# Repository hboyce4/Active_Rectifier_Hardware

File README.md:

Design files (Altium) for my bidirectional active rectifier. 

A Cortex-M4-driven bidirectional AC-DC power converter (active rectifier). 300W, 48VDC, 12VAC rms (through mains freq. step-down transformer). It should also be able to absorb/provide AC reactive power too. Its aim is more to be a test platform for control software than a useful/economical PSU. 

As of 2024-06-02, changes have been made to the inverter board but not incorporated into Altium because of a lack of license. They are:
 - PWModulator comparator output has been connected to GPIO PA.10 to measure duty cycle via a timer
 - U17, R56 and C87 have been removed as duty cycle is now measured digitally by a timer
 - R69 and R70 have been changed to 47 Ohm to improve rise time dramatically
 - R74, R76, R79 and R83 have all been changed to 1 Ohm to improve the power MOSFET's turn-off time

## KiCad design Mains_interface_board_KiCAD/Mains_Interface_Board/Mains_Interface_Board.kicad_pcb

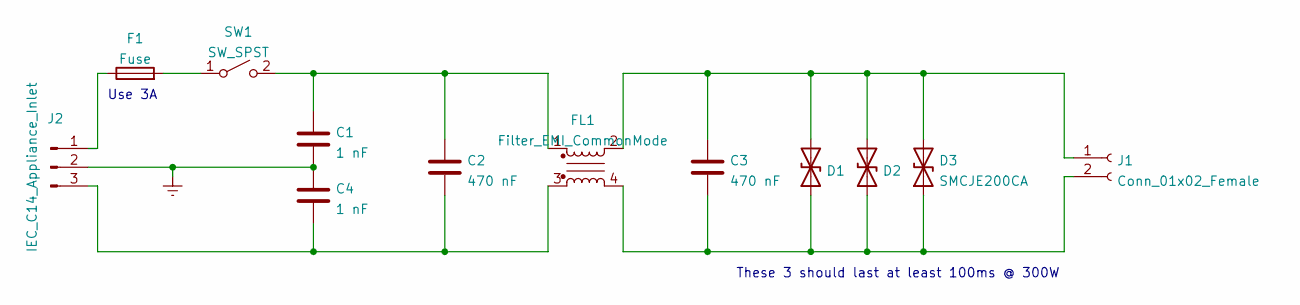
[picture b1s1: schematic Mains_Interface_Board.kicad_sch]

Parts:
C1, C4: 1 nF; C_Disc_D8.0mm_W5.0mm_P10.00mm
C2, C3: 470 nF; C_Rect_L26.5mm_W10.5mm_P22.50mm_MKS4
D1, D2, D3: SMCJE200CA; D_SMC
F1: Fuse; Fuseholder_Cylinder-6.3x30mm_Dual_Clips_Horizontal
FL1: Filter_EMI_CommonMode; Common_Mode_Choke_14x15mm
J1: Conn_01x02_Female; Dual_spades
J2: IEC_C14_Appliance_Inlet
SW1: SW_SPST; Dual_spades

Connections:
Earth: C1.2, C4.1, J2.2
unnamed: C1.1, C2.1, FL1.1, SW1.2 (B)
unnamed: C2.2, C4.2, FL1.3, J2.3
unnamed: C3.1, D1.2 (A2), D2.2 (A2), D3.2 (A2), FL1.2, J1.1
unnamed: C3.2, D1.1 (A1), D2.1 (A1), D3.1 (A1), FL1.4, J1.2
unnamed: F1.1, J2.1
unnamed: F1.2, SW1.1 (A)

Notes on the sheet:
Use 3A
These 3 should last at least 100ms @ 300W

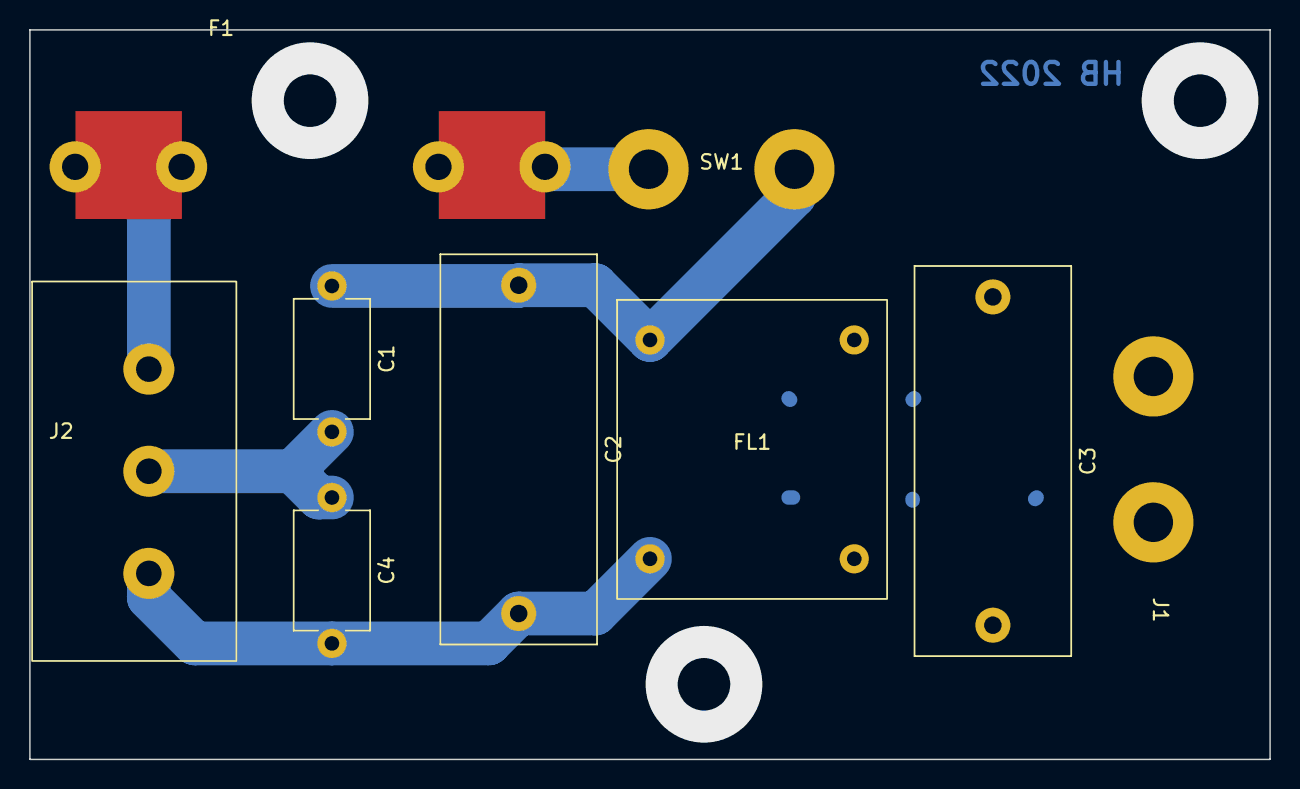
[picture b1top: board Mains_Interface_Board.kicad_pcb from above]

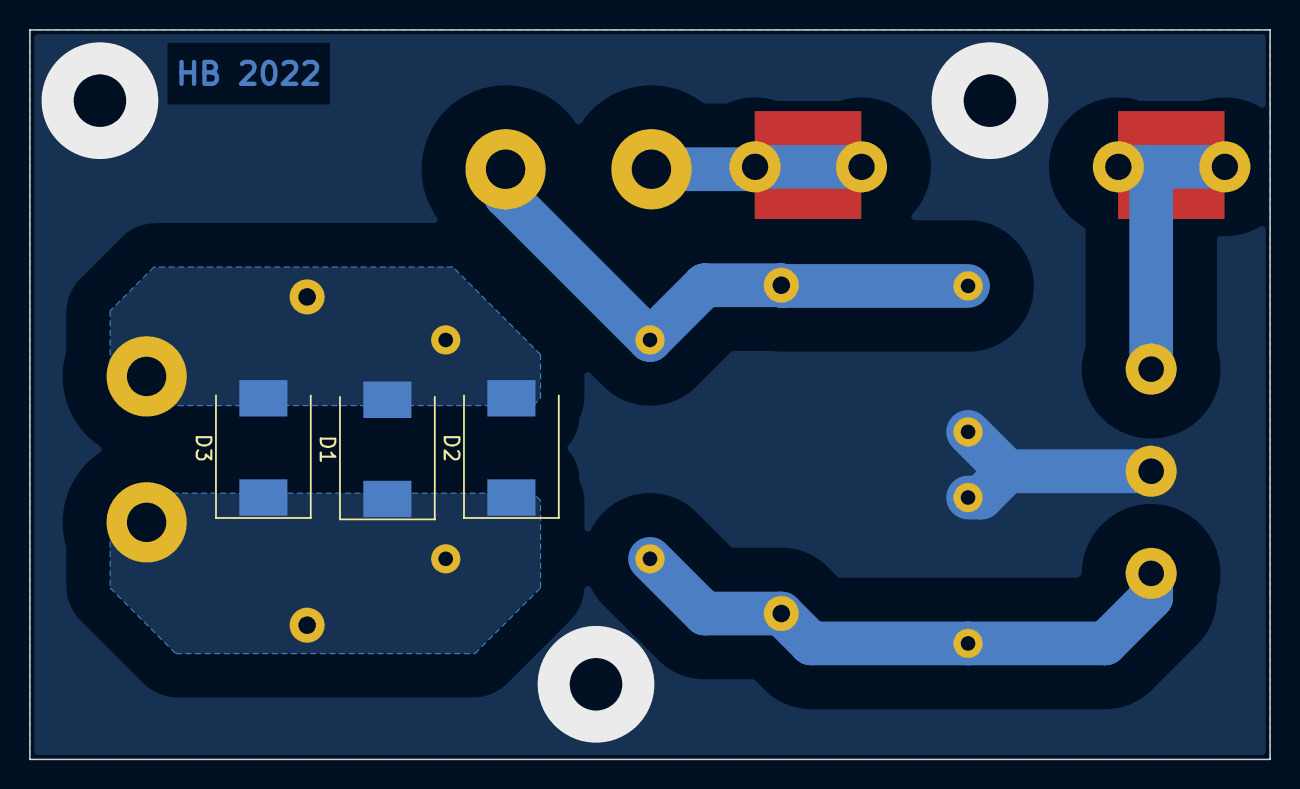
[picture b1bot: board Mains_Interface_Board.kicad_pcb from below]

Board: 2 copper layers, 85.0 x 50.0 mm, 12 parts (3 on the bottom side), 7 nets.

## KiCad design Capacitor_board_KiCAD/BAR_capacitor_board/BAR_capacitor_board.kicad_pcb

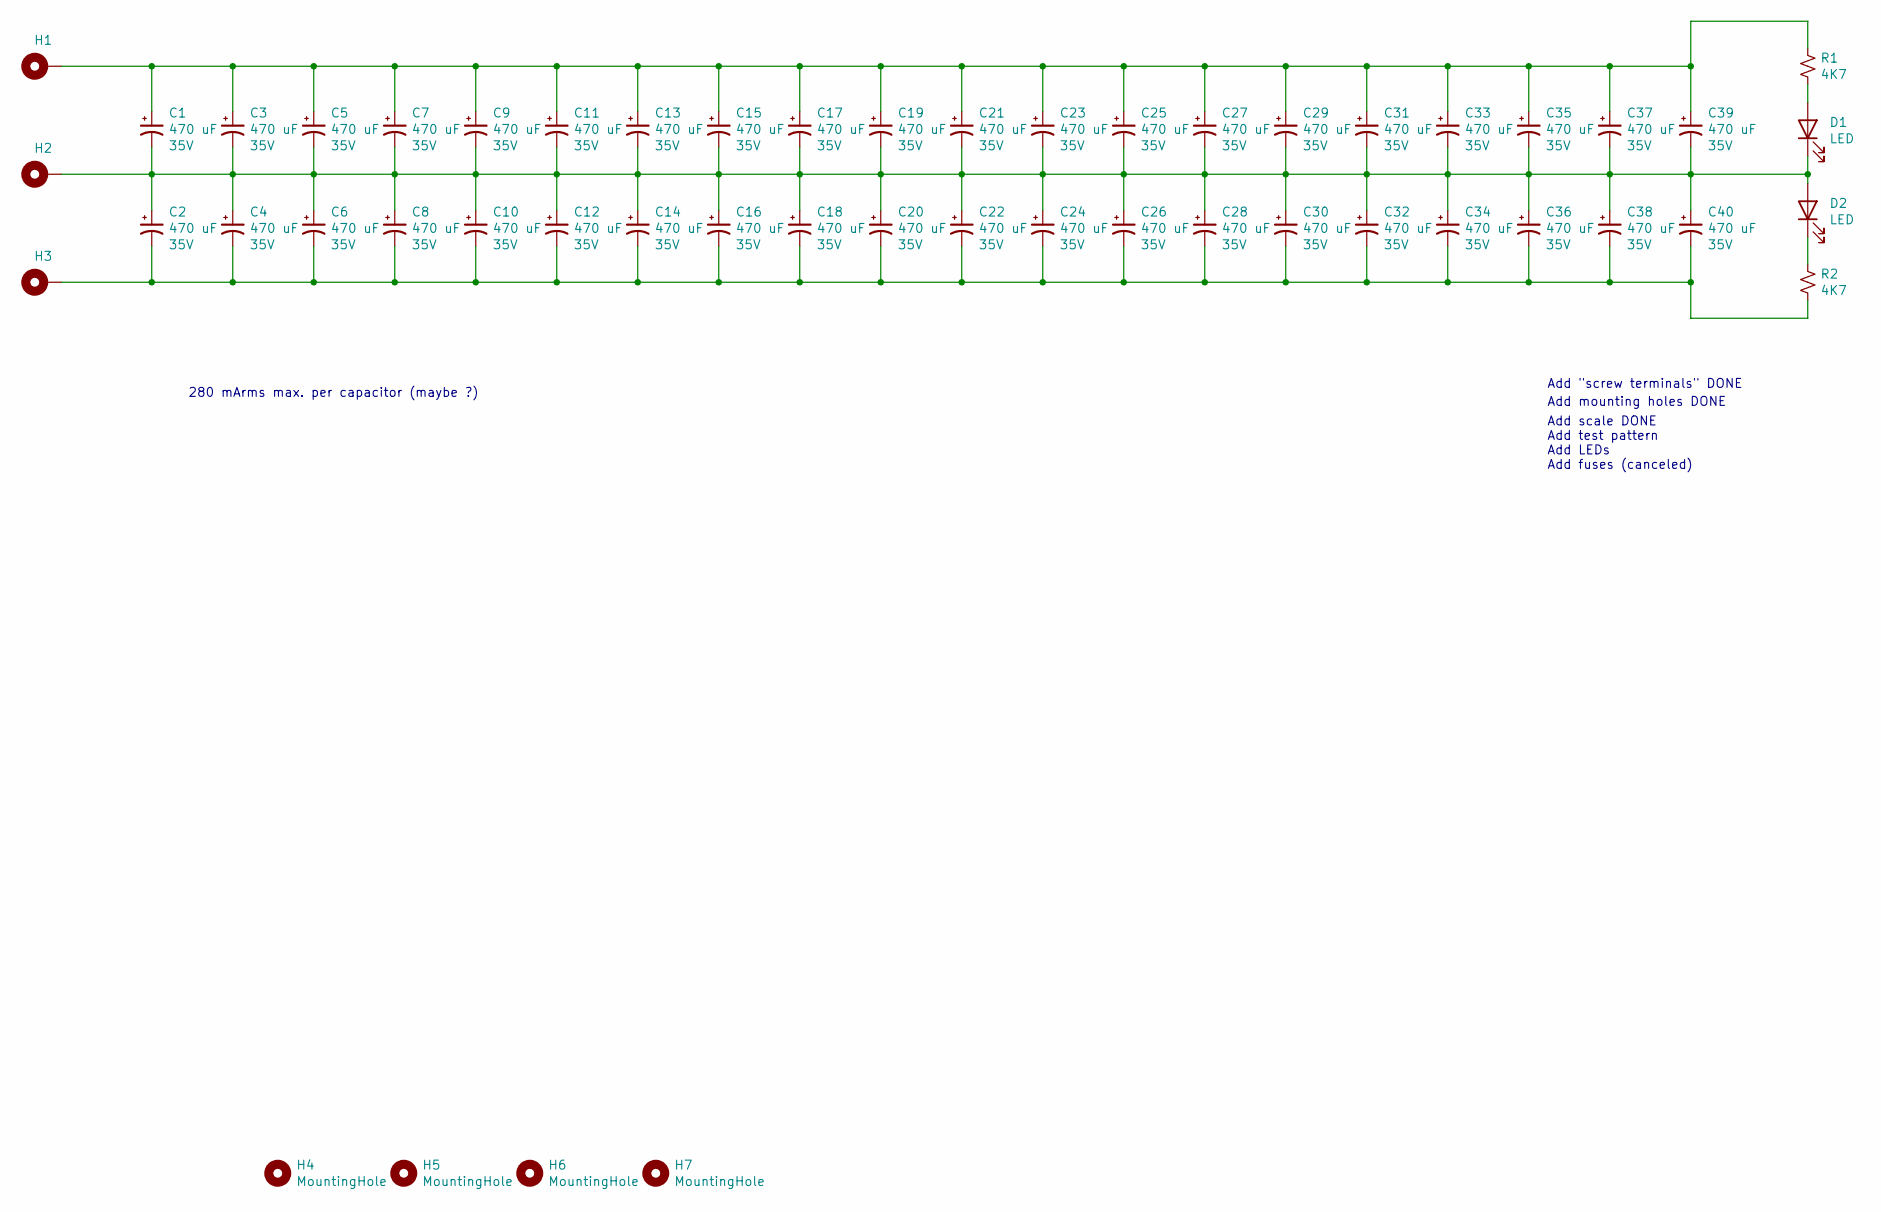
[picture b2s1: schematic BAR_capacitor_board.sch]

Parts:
C1, C2, C3, C4, C5, C6, C7, C8, C9, C10, C11, C12, C13, C14, C15, C16, C17, C18, C19, C20, C21, C22, C23, C24, C25, C26, C27, C28, C29, C30, C31, C32, C33, C34, C35, C36, C37, C38, C39, C40: 470 uF; CP_Elec_10x10.5; Max Voltage 35V
D1, D2: LED; LED_1206_3216Metric_Castellated
H1, H2, H3: MountingHole_Pad; SMD_REDCUBE_M4
H4, H5, H6, H7: MountingHole; MountingHole_3.2mm_M3_ISO14580_Pad
R1, R2: 4K7; R_1206_3216Metric

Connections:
unnamed: C1.1, C3.1, C5.1, C7.1, C9.1, C11.1, C13.1, C15.1, C17.1, C19.1, C21.1, C23.1, C25.1, C27.1, C29.1, C31.1, C33.1, C35.1, C37.1, C39.1, H1.1, R1.1
unnamed: C1.2, C2.1, C3.2, C4.1, C5.2, C6.1, C7.2, C8.1, C9.2, C10.1, C11.2, C12.1, C13.2, C14.1, C15.2, C16.1, C17.2, C18.1, C19.2, C20.1, C21.2, C22.1, C23.2, C24.1, C25.2, C26.1, C27.2, C28.1, C29.2, C30.1, C31.2, C32.1, C33.2, C34.1, C35.2, C36.1, C37.2, C38.1, C39.2, C40.1, D1.1 (K), D2.2 (A), H2.1
unnamed: C2.2, C4.2, C6.2, C8.2, C10.2, C12.2, C14.2, C16.2, C18.2, C20.2, C22.2, C24.2, C26.2, C28.2, C30.2, C32.2, C34.2, C36.2, C38.2, C40.2, H3.1, R2.2
unnamed: D1.2 (A), R1.2
unnamed: D2.1 (K), R2.1

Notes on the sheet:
Add mounting holes DONE
Add "screw terminals" DONE
280 mArms max. per capacitor (maybe ?)
Add scale DONE Add test pattern Add LEDs Add fuses (canceled)

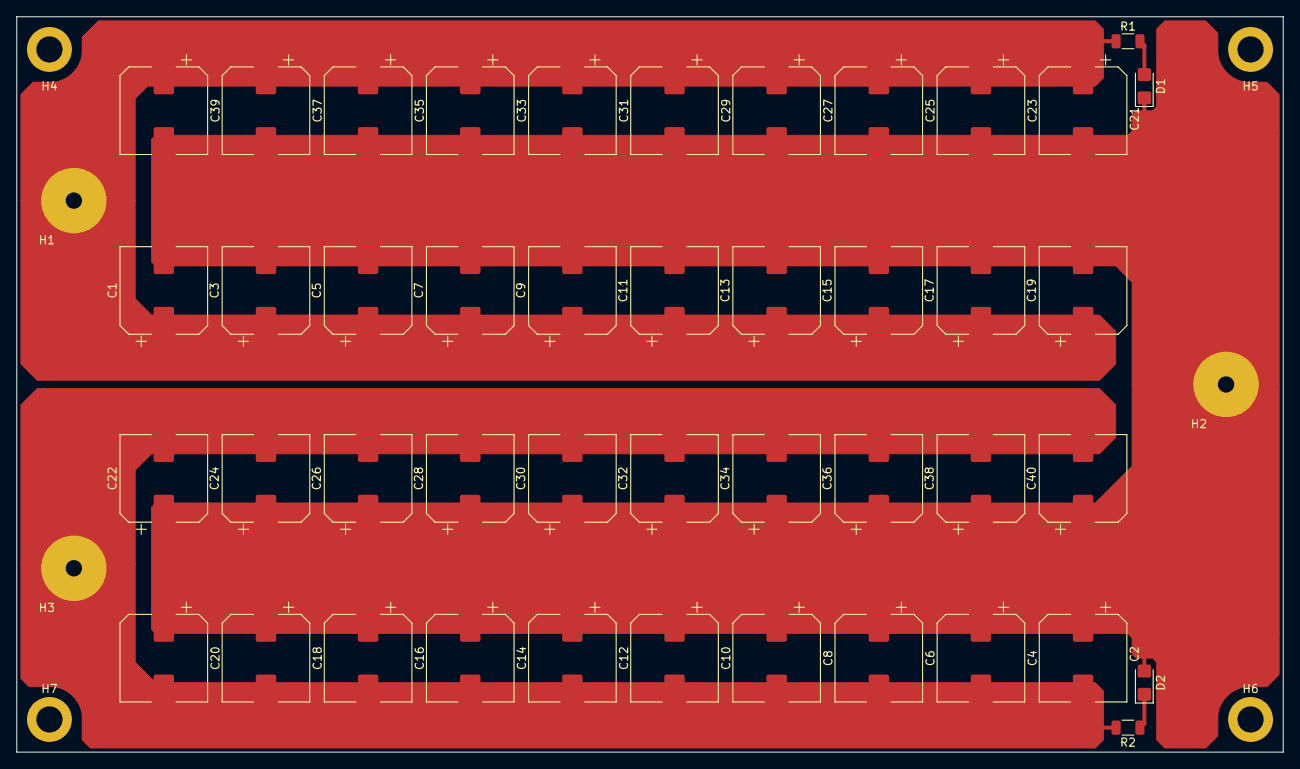
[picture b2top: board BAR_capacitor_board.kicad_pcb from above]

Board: 2 copper layers, 155.0 x 90.0 mm, 51 parts (0 on the bottom side), 5 nets.

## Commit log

2022-01-06 Added Files
    First real commit, adding all the files
2022-01-06 Edited Readme.md and updated project file
2022-01-07 Finished logical groupings
    And fixed some footprints
2022-01-08 Rough placement of the power section done
    Design rules added as per OSHPark rules (JLCPCB less stringent). Net classes created and the net attribution for them was started.
2022-01-10 Small additions
    First polygon pour added
2022-01-11 Added most pours for the power section
2022-01-13 Fixed classes. Improved board outlines. Changed some placement
2022-01-14 Lower section of board *almost* finished
    Placed and routed
2022-01-17 Finalized the lower portion
2022-01-17 Started upper portion
2022-01-18 Changed connectors to SMD
2022-01-20 Advanced placement and routing of upper portion
2022-01-21 Advanced upper portion
    Upper right almost finished. Board dimensions final at 95mm x 135mm
2022-01-21 Analog section and silk left
    Almost everything else is done
2022-01-24 Finished routing messily
    And cleared some errors
2022-01-24 Improved analog section, changed some footprints to clear some errors
2022-01-25 Finished
    Silkscreen is all cute and everything.
2022-01-25 Changed some footprints and parameters to export the BOM
2022-01-26 Comparator and annotation change
    Comparators changed to use the much more popular SOT-23-5 footprint. Whole board reannotated for convenience. Re-exported BOM and PDF.
2022-01-26 Simplified path
2022-01-26 Exported gerber files
    Fixed 33 pF caps for the BOM as well.
2022-04-14 Added files for Capacitor and Mains interface boards
    Those were made using KiCAD
2022-05-09 Added TODO
    Add teardrops!
2024-06-03 Added a list of hardware modifications to the readme
